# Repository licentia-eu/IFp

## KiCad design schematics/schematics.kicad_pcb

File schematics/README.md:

# Interface 3.14 schematics

Based on [zx-spectrum-pico-rom](https://github.com/derekfountain/zx-spectrum-pico-rom)

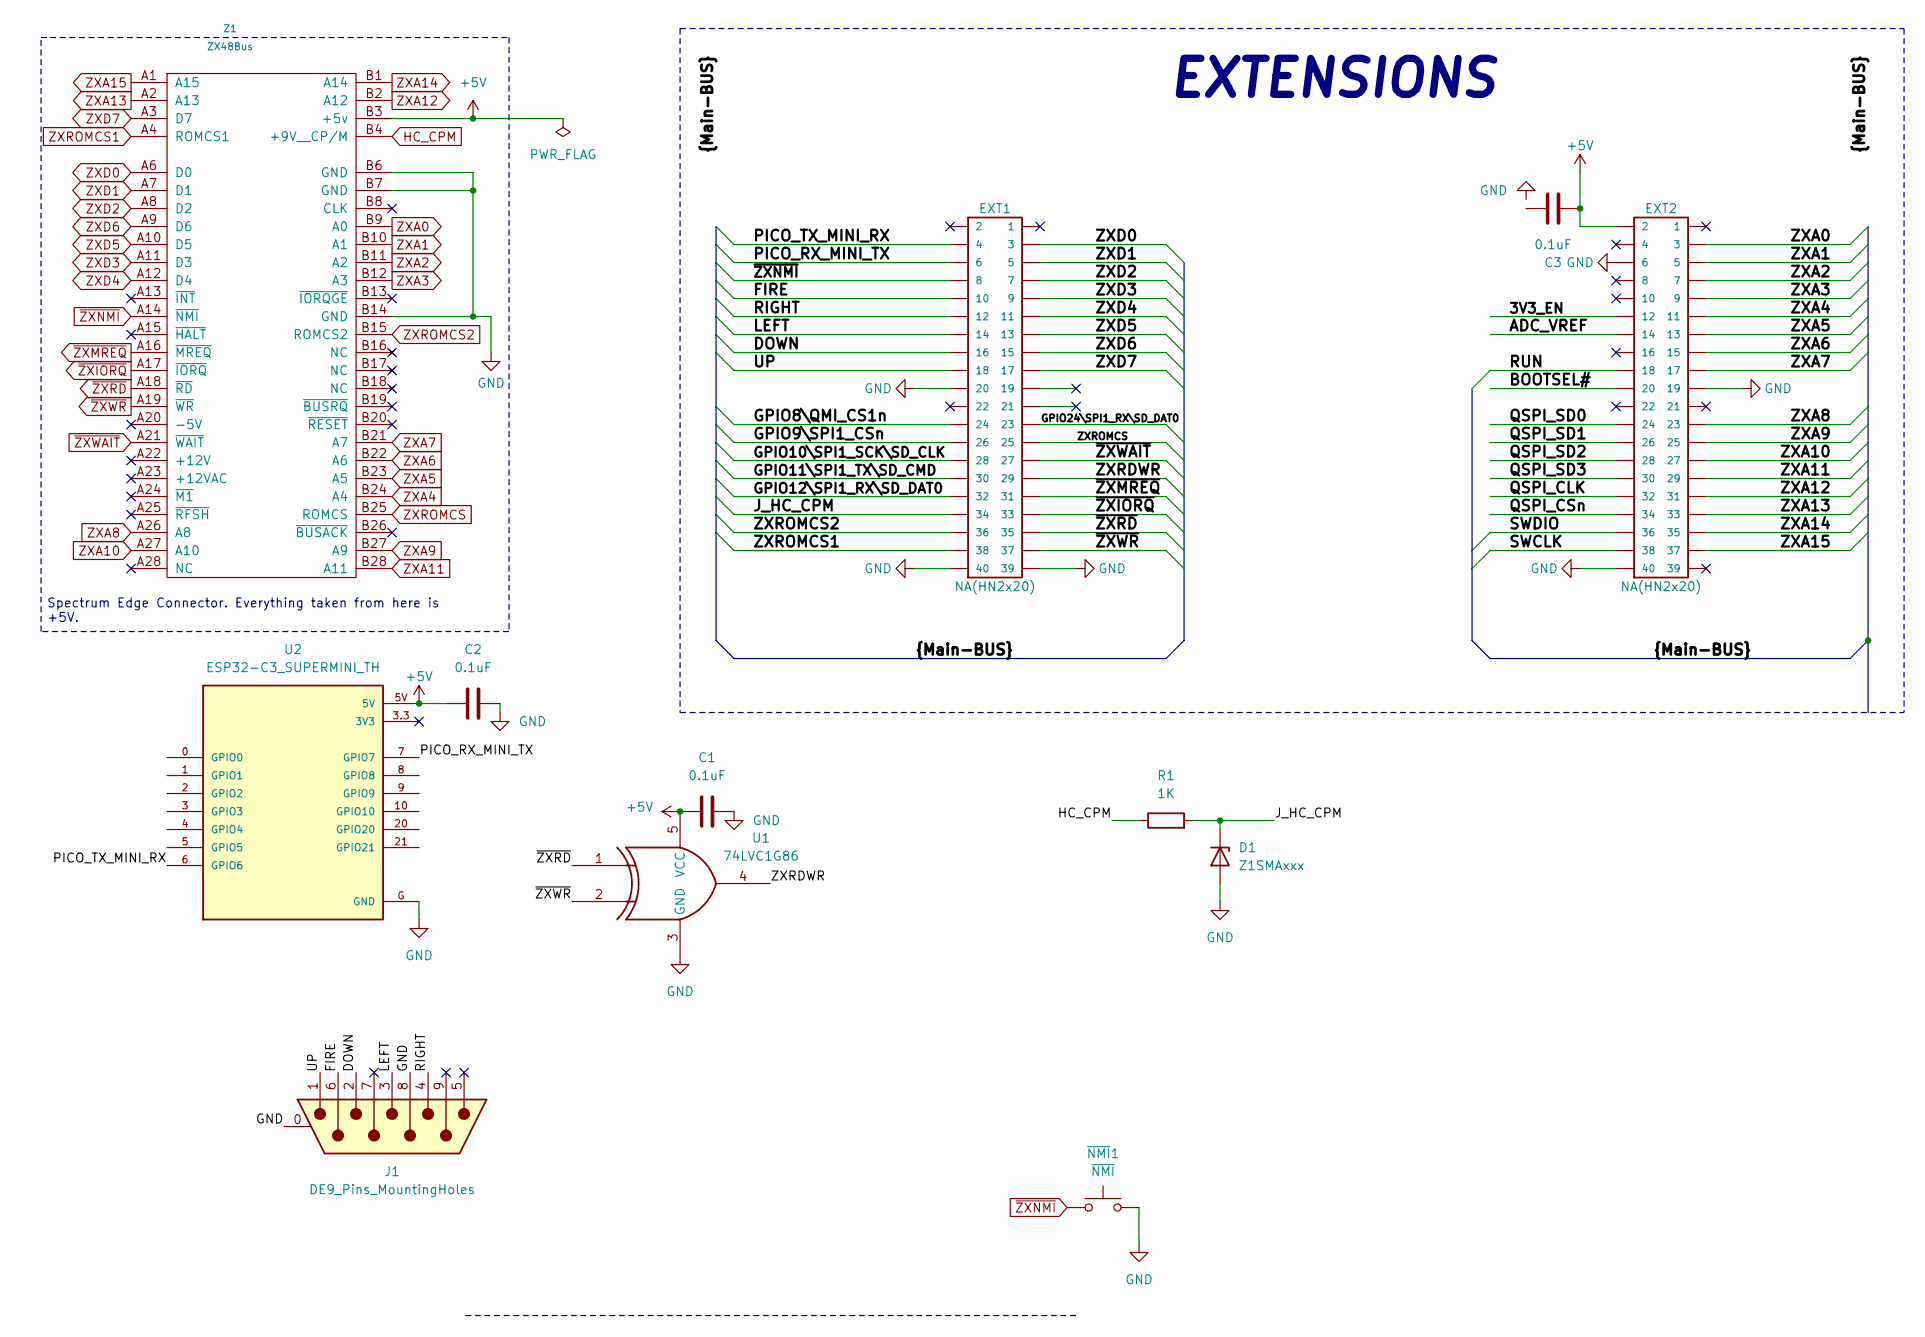
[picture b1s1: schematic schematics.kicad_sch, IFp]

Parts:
C1, C2, C3: 0.1uF; C_1210_3225Metric
D1: Z1SMAxxx; D_SMA
EXT1, EXT2: NA(HN2x20); HN2x20
J1: DE9_Pins_MountingHoles; DSUB-9_Pins_Horizontal_P2.77x2.84mm_EdgePinOffset4.94mm_Hou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
R1: 1K; R_0805_2012Metric
U1: 74LVC1G86; SOT-353_SC-70-5; LCSC PN C52350
U2: ESP32-C3_SUPERMINI_TH; MODULE_ESP32-C3_SUPERMINI_TH
Z1: ZX48Bus; ZX_Bus_Edge_Connector
~{NMI}1: ~{NMI}; SW_Tactile_SKHH_Angled

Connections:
+5V: C1.1, C2.1, C3.1, EXT2.2, U1.5 (VCC), U2.5V, Z1.B3 (+5v)
/3V3_EN: EXT2.12
/ADC_VREF: EXT2.14
/BOOTSEL#: EXT2.20
/DOWN: EXT1.16, J1.2
/FIRE: EXT1.10, J1.6
/GPIO8\QMI_CS1n: EXT1.24
/GPIO9\SPI1_CSn: EXT1.26
/GPIO10\SPI1_SCK\SD_CLK: EXT1.28
/GPIO11\SPI1_TX\SD_CMD: EXT1.30
/GPIO12\SPI1_RX\SD_DAT0: EXT1.32
/GPIO24\SPI1_RX\SD_DAT0: EXT1.23
/J_HC_CPM: D1.1 (K), EXT1.34, R1.2
/LEFT: EXT1.14, J1.3
/PICO_RX_MINI_TX: EXT1.6, U2.7 (GPIO7)
/PICO_TX_MINI_RX: EXT1.4, U2.6 (GPIO6)
/QSPI_CLK: EXT2.32
/QSPI_CSn: EXT2.34
/QSPI_SD0: EXT2.24
/QSPI_SD1: EXT2.26
/QSPI_SD2: EXT2.28
/QSPI_SD3: EXT2.30
/RIGHT: EXT1.12, J1.4
/RUN: EXT2.18
/SWCLK: EXT2.38
/SWDIO: EXT2.36
/UP: EXT1.18, J1.1
/ZXRDWR: EXT1.29, U1.4
GND: C1.2, C2.2, D1.2 (A), EXT1.20, EXT1.39, EXT1.40, EXT2.6, EXT2.19, EXT2.40, J1.0 (PAD), J1.8, U1.3 (GND), U2.G (GND), Z1.B6 (GND), Z1.B7 (GND), Z1.B14 (GND), ~{NMI}1.2
HC_CPM: R1.1, Z1.B4 (+9V__CP/M)
ZXA0: EXT2.3, Z1.B9 (A0)
ZXA1: EXT2.5, Z1.B10 (A1)
ZXA2: EXT2.7, Z1.B11 (A2)
ZXA3: EXT2.9, Z1.B12 (A3)
ZXA4: EXT2.11, Z1.B24 (A4)
ZXA5: EXT2.13, Z1.B23 (A5)
ZXA6: EXT2.15, Z1.B22 (A6)
ZXA7: EXT2.17, Z1.B21 (A7)
ZXA8: EXT2.23, Z1.A26 (A8)
ZXA9: EXT2.25, Z1.B27 (A9)
ZXA10: EXT2.27, Z1.A27 (A10)
ZXA11: EXT2.29, Z1.B28 (A11)
ZXA12: EXT2.31, Z1.B2 (A12)
ZXA13: EXT2.33, Z1.A2 (A13)
ZXA14: EXT2.35, Z1.B1 (A14)
ZXA15: EXT2.37, Z1.A1 (A15)
ZXD0: EXT1.3, Z1.A6 (D0)
ZXD1: EXT1.5, Z1.A7 (D1)
ZXD2: EXT1.7, Z1.A8 (D2)
ZXD3: EXT1.9, Z1.A11 (D3)
ZXD4: EXT1.11, Z1.A12 (D4)
ZXD5: EXT1.13, Z1.A10 (D5)
ZXD6: EXT1.15, Z1.A9 (D6)
ZXD7: EXT1.17, Z1.A3 (D7)
ZXROMCS: EXT1.25, Z1.B25 (ROMCS)
ZXROMCS1: EXT1.38, Z1.A4 (ROMCS1)
ZXROMCS2: EXT1.36, Z1.B15 (ROMCS2)
~ZXIORQ: EXT1.33, Z1.A17 (~IORQ)
~ZXMREQ: EXT1.31, Z1.A16 (~MREQ)
~ZXNMI: EXT1.8, Z1.A14 (~NMI), ~{NMI}1.1
~ZXRD: EXT1.35, U1.1, Z1.A18 (~RD)
~ZXWAIT: EXT1.27, Z1.A21 (~WAIT)
~ZXWR: EXT1.37, U1.2, Z1.A19 (~WR)

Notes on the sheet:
EXTENSIONS
Spectrum Edge Connector. Everything taken from here is +5V.

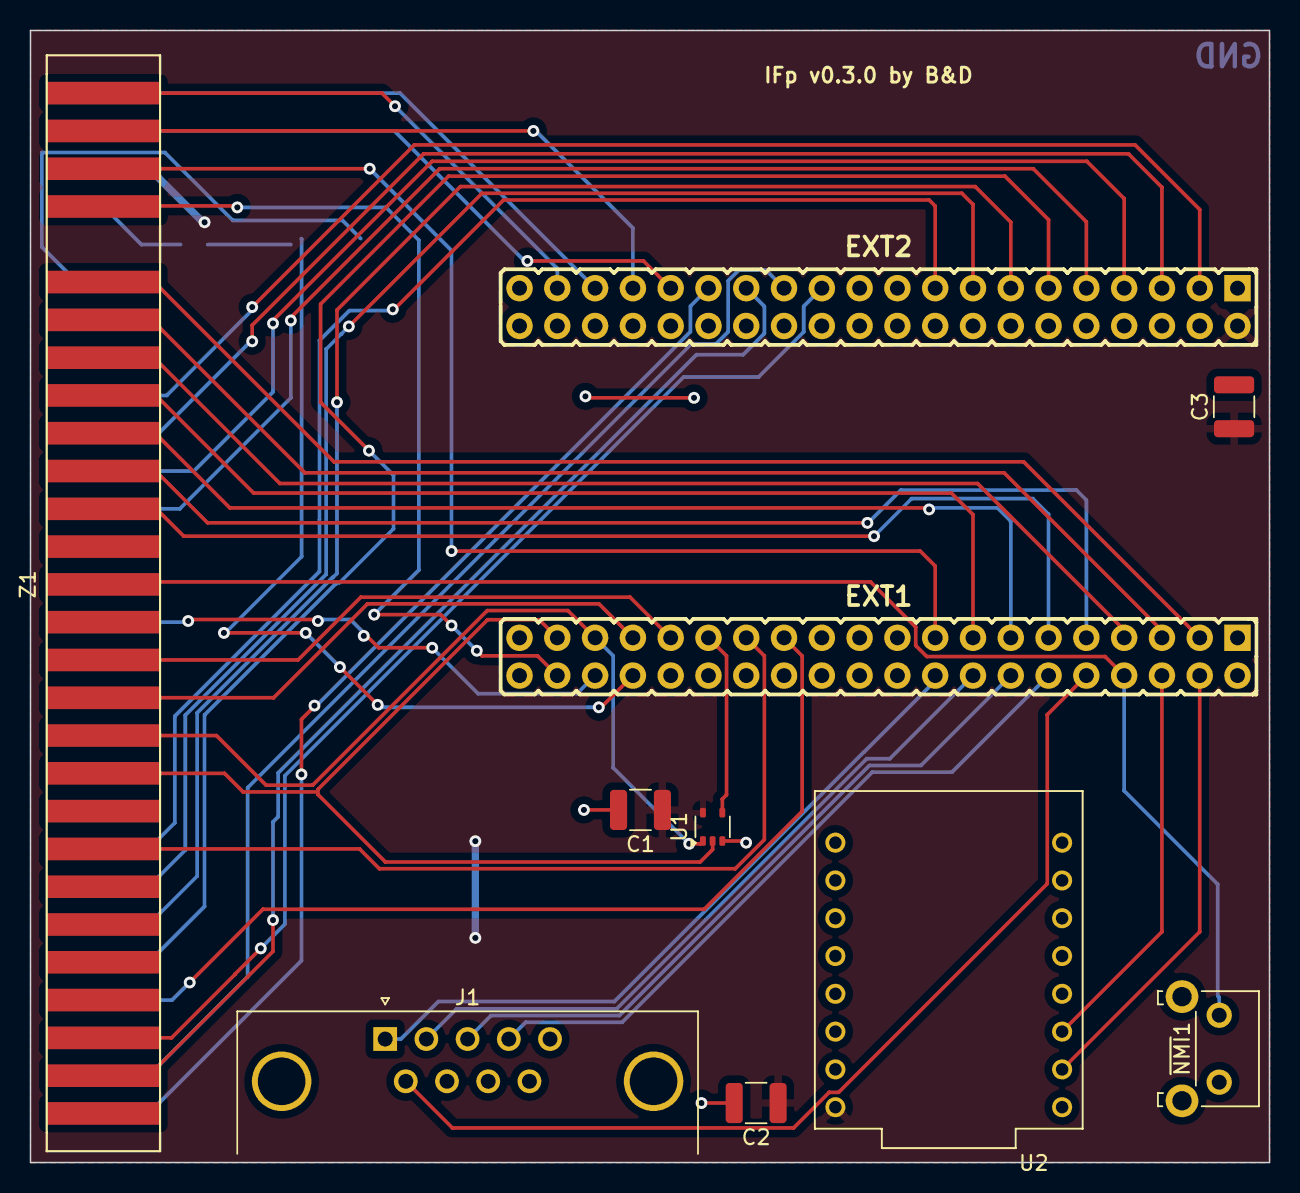
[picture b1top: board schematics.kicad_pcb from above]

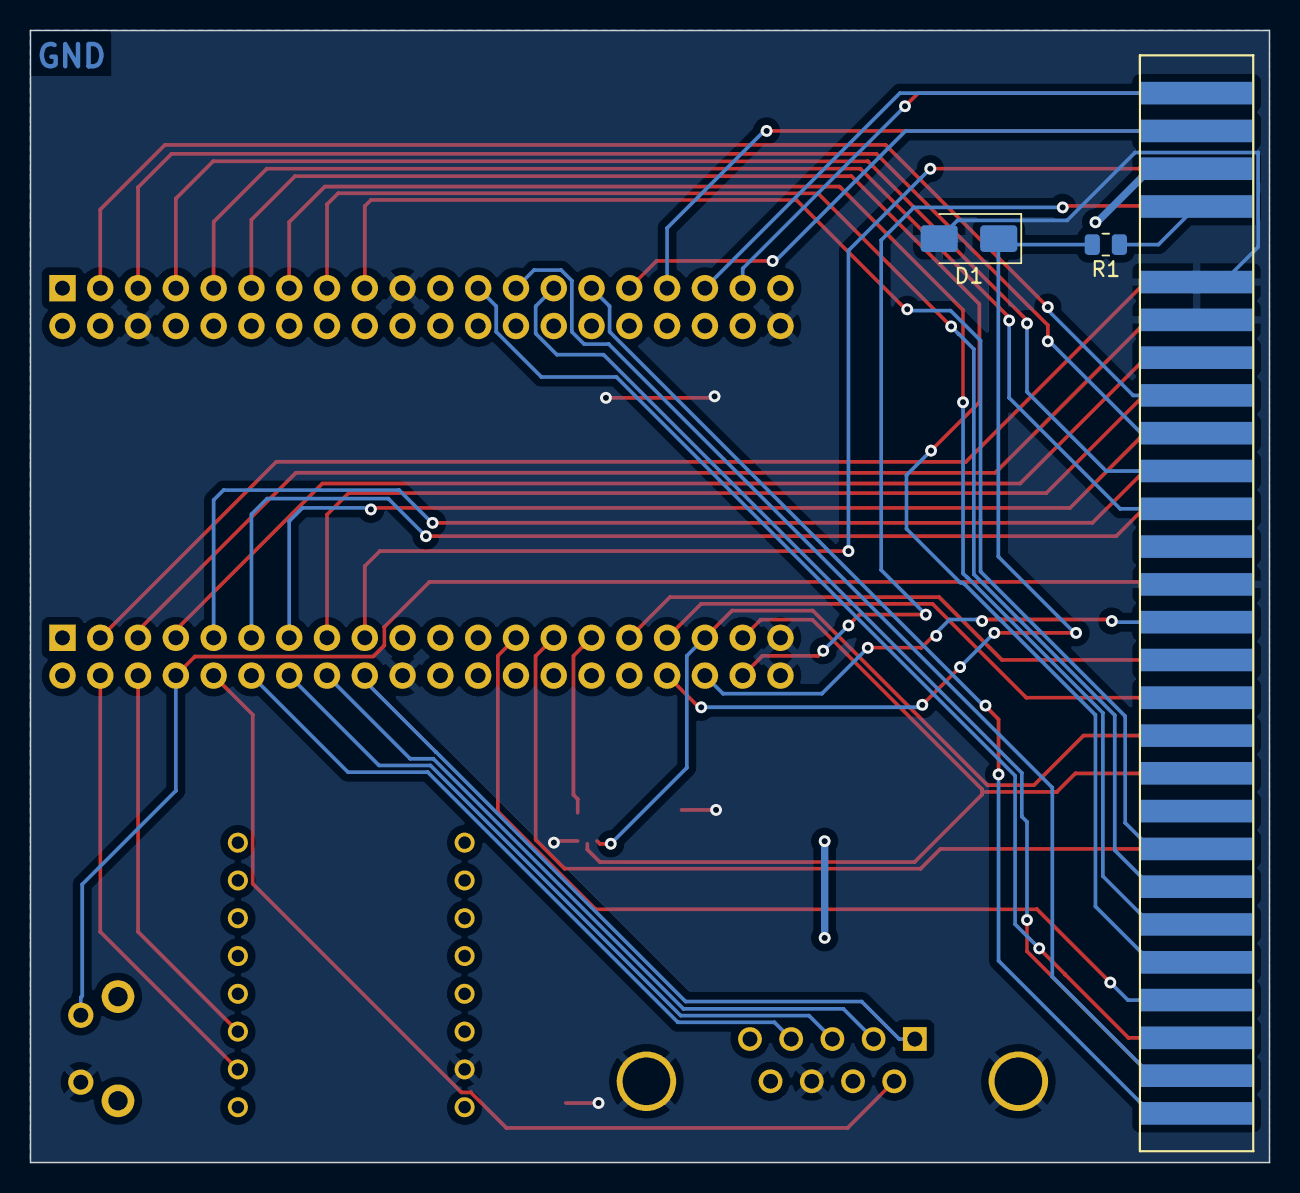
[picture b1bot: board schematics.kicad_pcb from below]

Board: 2 copper layers, 83.3 x 76.1 mm, 11 parts (2 on the bottom side), 45 nets.

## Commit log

2024-04-25 More tests
2024-04-25 Add docs
2024-04-25 Fix schematics
2024-04-26 Fix 74xx245 naming
2025-06-20 add adc
2025-07-04 Switched to olimex pico2 xxl
2025-07-10 Add Olimex rp2350 stub
2025-07-10 Fix BogDan is an idiot wrong line assignment
    Fixes: #1, #3
2025-07-11 Add kempston joystick
